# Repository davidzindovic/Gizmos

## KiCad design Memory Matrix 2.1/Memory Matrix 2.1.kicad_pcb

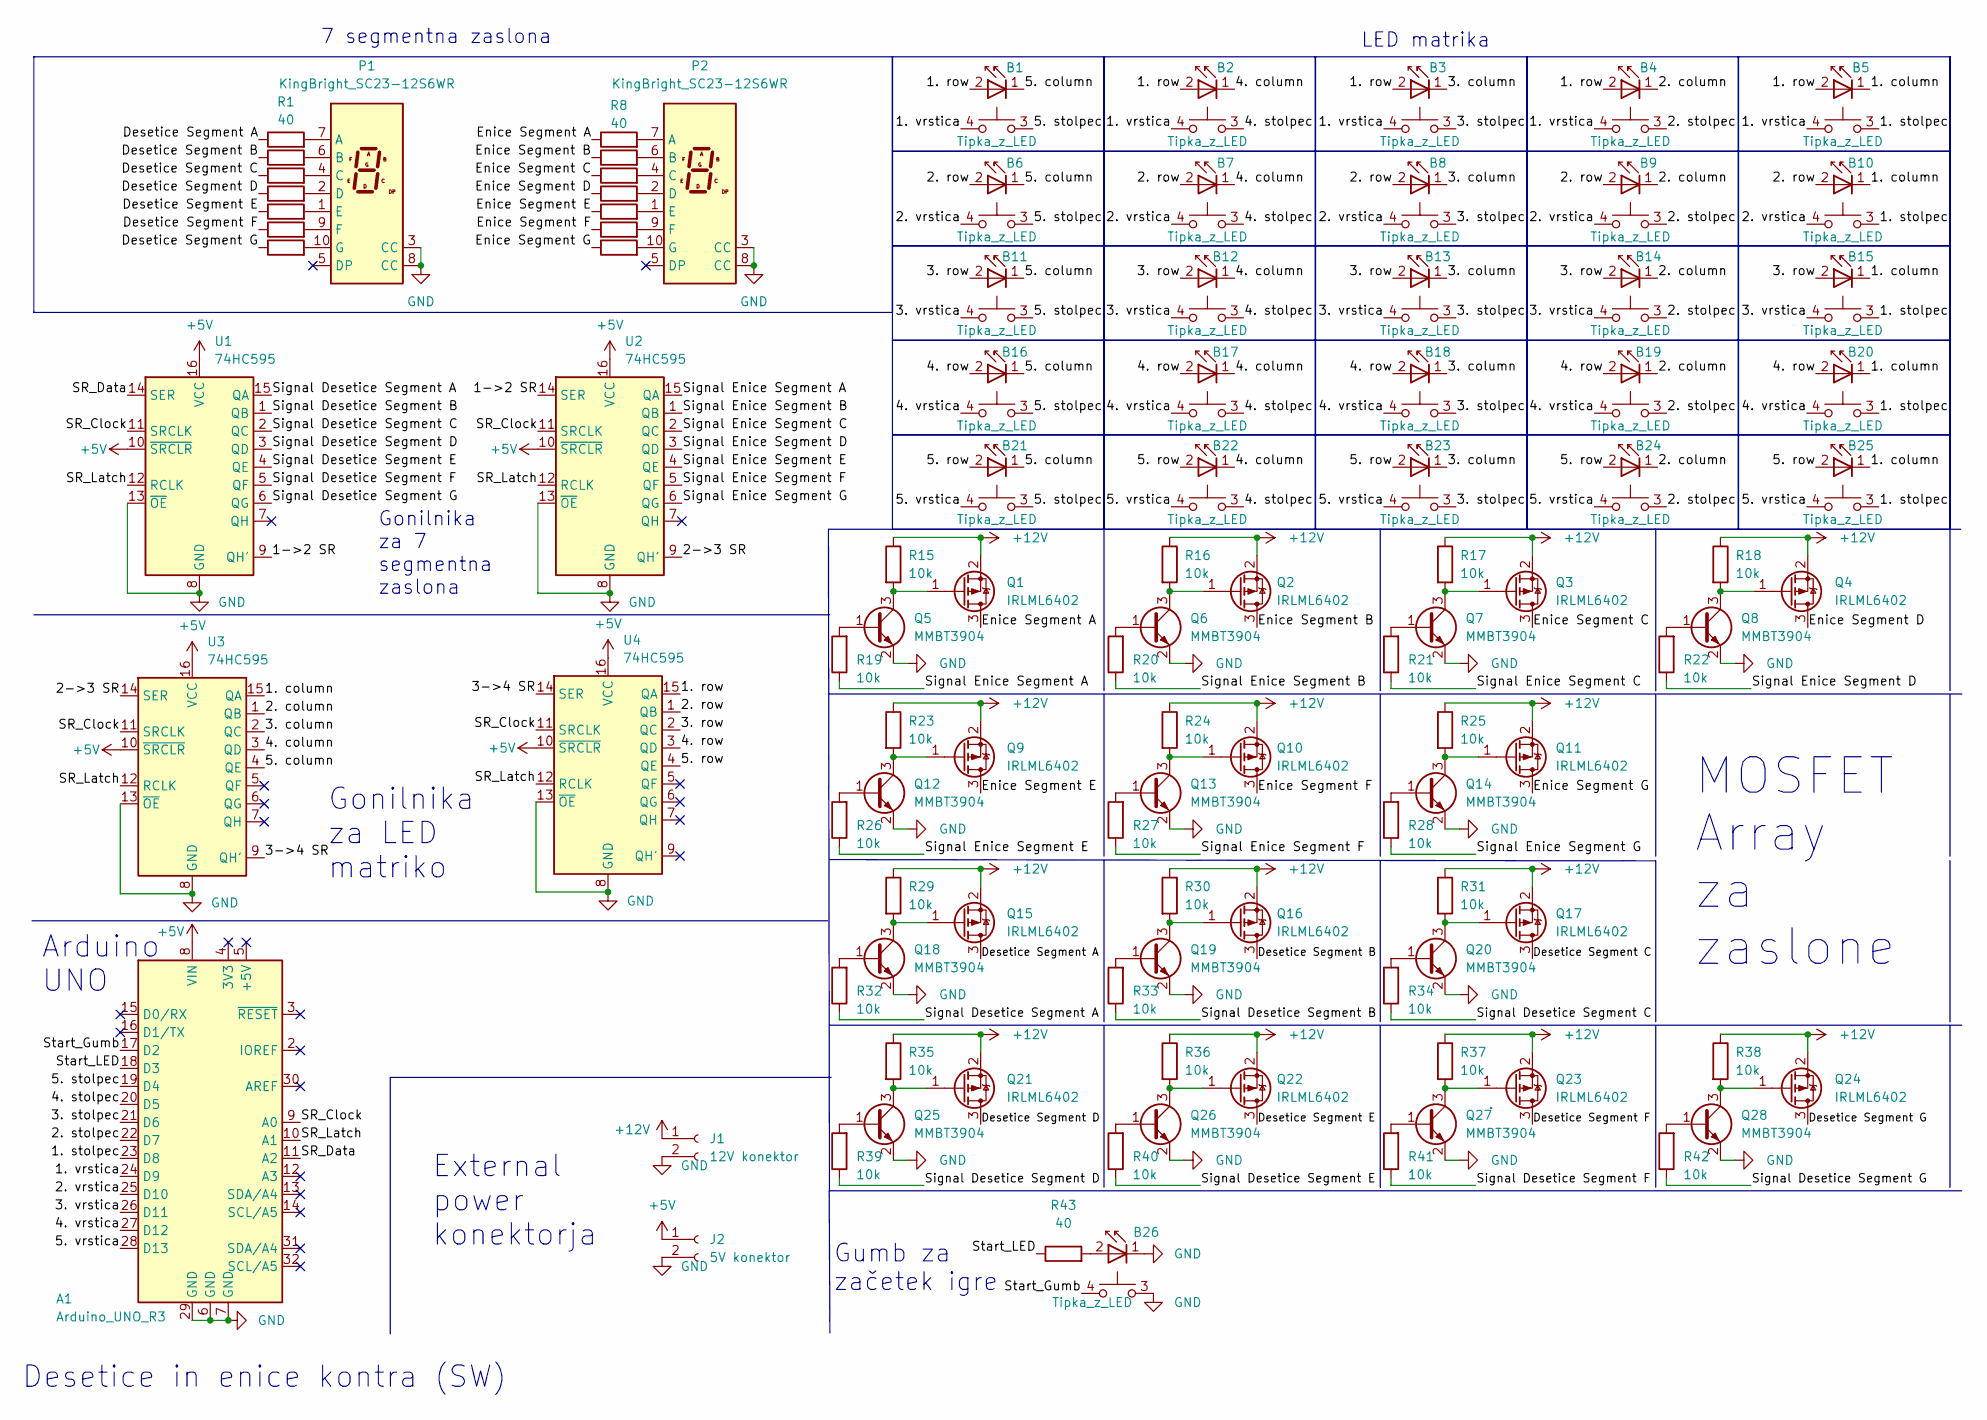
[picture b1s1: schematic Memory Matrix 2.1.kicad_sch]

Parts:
A1: Arduino_UNO_R3; Arduino_UNO_R3_WithMountingHoles
B1, B2, B3, B4, B5, B6, B7, B8, B9, B10, B11, B12, B13, B14, B15, B16, B17, B18, B19, B20, B21, B22, B23, B24, B25: Tipka_z_LED; Phoenix 4 pin z natičom
B26: Tipka_z_LED; PhoenixContact_MC_1,5_4-GF-3.81_1x04_P3.81mm_Horizontal_Thr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
J1: 12V konektor; PhoenixContact_MCV_1,5_2-GF-3.81_1x02_P3.81mm_Vertical_Thre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
J2: 5V konektor; PhoenixContact_MCV_1,5_2-GF-3.81_1x02_P3.81mm_Vertical_Thre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
P1, P2: KingBright_SC23-12S6WR; KingBright SC23-12S6WR
Q1, Q2, Q3, Q4, Q9, Q10, Q11, Q15, Q16, Q17, Q21, Q22, Q23, Q24: IRLML6402; SOT-23
Q5, Q6, Q7, Q8, Q12, Q13, Q14, Q18, Q19, Q20, Q25, Q26, Q27, Q28: MMBT3904; SOT-23
R1, R2, R3, R4, R5, R6, R7, R8, R9, R10, R11, R12, R13, R14, R43: 40; R_0805_2012Metric
R15, R16, R17, R18, R19, R20, R21, R22, R23, R24, R25, R26, R27, R28, R29, R30, R31, R32, R33, R34, R35, R36, R37, R38, R39, R40, R41, R42: 10k; R_0805_2012Metric
U1, U2, U3, U4: 74HC595; SOIC-16_3.9x9.9mm_P1.27mm

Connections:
+5V: A1.8 (VIN), J2.1, U1.10 (~SRCLR), U1.16 (VCC), U2.10 (~SRCLR), U2.16 (VCC), U3.10 (~SRCLR), U3.16 (VCC), U4.10 (~SRCLR), U4.16 (VCC)
+12V: J1.1, Q1.2 (S), Q2.2 (S), Q3.2 (S), Q4.2 (S), Q9.2 (S), Q10.2 (S), Q11.2 (S), Q15.2 (S), Q16.2 (S), Q17.2 (S), Q21.2 (S), Q22.2 (S), Q23.2 (S), Q24.2 (S), R15.1, R16.1, R17.1, R18.1, R23.1, R24.1, R25.1, R29.1, R30.1, R31.1, R35.1, R36.1, R37.1, R38.1
/1->2 SR: U1.9 (QH'), U2.14 (SER)
/1. column: B5.1, B10.1, B15.1, B20.1, B25.1, U3.15 (QA)
/1. row: B1.2, B2.2, B3.2, B4.2, B5.2, U4.15 (QA)
/1. stolpec: A1.23 (D8), B5.3, B10.3, B15.3, B20.3, B25.3
/1. vrstica: A1.24 (D9), B1.4, B2.4, B3.4, B4.4, B5.4
/2->3 SR: U2.9 (QH'), U3.14 (SER)
/2. column: B4.1, B9.1, B14.1, B19.1, B24.1, U3.1 (QB)
/2. row: B6.2, B7.2, B8.2, B9.2, B10.2, U4.1 (QB)
/2. stolpec: A1.22 (D7), B4.3, B9.3, B14.3, B19.3, B24.3
/2. vrstica: A1.25 (D10), B6.4, B7.4, B8.4, B9.4, B10.4
/3->4 SR: U3.9 (QH'), U4.14 (SER)
/3. column: B3.1, B8.1, B13.1, B18.1, B23.1, U3.2 (QC)
/3. row: B11.2, B12.2, B13.2, B14.2, B15.2, U4.2 (QC)
/3. stolpec: A1.21 (D6), B3.3, B8.3, B13.3, B18.3, B23.3
/3. vrstica: A1.26 (D11), B11.4, B12.4, B13.4, B14.4, B15.4
/4. column: B2.1, B7.1, B12.1, B17.1, B22.1, U3.3 (QD)
/4. row: B16.2, B17.2, B18.2, B19.2, B20.2, U4.3 (QD)
/4. stolpec: A1.20 (D5), B2.3, B7.3, B12.3, B17.3, B22.3
/4. vrstica: A1.27 (D12), B16.4, B17.4, B18.4, B19.4, B20.4
/5. column: B1.1, B6.1, B11.1, B16.1, B21.1, U3.4 (QE)
/5. row: B21.2, B22.2, B23.2, B24.2, B25.2, U4.4 (QE)
/5. stolpec: A1.19 (D4), B1.3, B6.3, B11.3, B16.3, B21.3
/5. vrstica: A1.28 (D13), B21.4, B22.4, B23.4, B24.4, B25.4
/Desetice Segment A: Q15.3 (D), R1.1
/Desetice Segment B: Q16.3 (D), R2.1
/Desetice Segment C: Q17.3 (D), R3.1
/Desetice Segment D: Q21.3 (D), R4.1
/Desetice Segment E: Q22.3 (D), R5.1
/Desetice Segment F: Q23.3 (D), R6.1
/Desetice Segment G: Q24.3 (D), R7.1
/Enice Segment A: Q1.3 (D), R8.1
/Enice Segment B: Q2.3 (D), R9.1
/Enice Segment C: Q3.3 (D), R10.1
/Enice Segment D: Q4.3 (D), R11.1
/Enice Segment E: Q9.3 (D), R12.1
/Enice Segment F: Q10.3 (D), R13.1
/Enice Segment G: Q11.3 (D), R14.1
/SR_Clock: A1.9 (A0), U1.11 (SRCLK), U2.11 (SRCLK), U3.11 (SRCLK), U4.11 (SRCLK)
/SR_Data: A1.11 (A2), U1.14 (SER)
/SR_Latch: A1.10 (A1), U1.12 (RCLK), U2.12 (RCLK), U3.12 (RCLK), U4.12 (RCLK)
/Signal Desetice Segment A: R32.1, U1.15 (QA)
/Signal Desetice Segment B: R33.1, U1.1 (QB)
/Signal Desetice Segment C: R34.1, U1.2 (QC)
/Signal Desetice Segment D: R39.1, U1.3 (QD)
/Signal Desetice Segment E: R40.1, U1.4 (QE)
/Signal Desetice Segment F: R41.1, U1.5 (QF)
/Signal Desetice Segment G: R42.1, U1.6 (QG)
/Signal Enice Segment A: R19.1, U2.15 (QA)
/Signal Enice Segment B: R20.1, U2.1 (QB)
/Signal Enice Segment C: R21.1, U2.2 (QC)
/Signal Enice Segment D: R22.1, U2.3 (QD)
/Signal Enice Segment E: R26.1, U2.4 (QE)
/Signal Enice Segment F: R27.1, U2.5 (QF)
/Signal Enice Segment G: R28.1, U2.6 (QG)
/Start_Gumb: A1.17 (D2), B26.4
/Start_LED: A1.18 (D3), R43.1
GND: A1.6 (GND), A1.7 (GND), A1.29 (GND), B26.1, B26.3, J1.2, J2.2, P1.3 (CC), P1.8 (CC), P2.3 (CC), P2.8 (CC), Q5.2 (E), Q6.2 (E), Q7.2 (E), Q8.2 (E), Q12.2 (E), Q13.2 (E), Q14.2 (E), Q18.2 (E), Q19.2 (E), Q20.2 (E), Q25.2 (E), Q26.2 (E), Q27.2 (E), Q28.2 (E), U1.8 (GND), U1.13 (~OE), U2.8 (GND), U2.13 (~OE), U3.8 (GND), U3.13 (~OE), U4.8 (GND), U4.13 (~OE)
unnamed: B26.2, R43.2
unnamed: P1.1 (E), R5.2
unnamed: P1.2 (D), R4.2
unnamed: P1.4 (C), R3.2
unnamed: P1.6 (B), R2.2
unnamed: P1.7 (A), R1.2
unnamed: P1.9 (F), R6.2
unnamed: P1.10 (G), R7.2
unnamed: P2.1 (E), R12.2
unnamed: P2.2 (D), R11.2
unnamed: P2.4 (C), R10.2
unnamed: P2.6 (B), R9.2
unnamed: P2.7 (A), R8.2
unnamed: P2.9 (F), R13.2
unnamed: P2.10 (G), R14.2
unnamed: Q1.1 (G), Q5.3 (C), R15.2
unnamed: Q2.1 (G), Q6.3 (C), R16.2
unnamed: Q3.1 (G), Q7.3 (C), R17.2
unnamed: Q4.1 (G), Q8.3 (C), R18.2
unnamed: Q5.1 (B), R19.2
unnamed: Q6.1 (B), R20.2
unnamed: Q7.1 (B), R21.2
unnamed: Q8.1 (B), R22.2
unnamed: Q10.1 (G), Q13.3 (C), R24.2
unnamed: Q11.1 (G), Q14.3 (C), R25.2
unnamed: Q12.1 (B), R26.2
unnamed: Q9.1 (G), Q12.3 (C), R23.2
unnamed: Q13.1 (B), R27.2
unnamed: Q14.1 (B), R28.2
unnamed: Q15.1 (G), Q18.3 (C), R29.2
unnamed: Q16.1 (G), Q19.3 (C), R30.2
unnamed: Q17.1 (G), Q20.3 (C), R31.2
unnamed: Q18.1 (B), R32.2
unnamed: Q19.1 (B), R33.2
unnamed: Q20.1 (B), R34.2
unnamed: Q21.1 (G), Q25.3 (C), R35.2
unnamed: Q22.1 (G), Q26.3 (C), R36.2
unnamed: Q23.1 (G), Q27.3 (C), R37.2
unnamed: Q24.1 (G), Q28.3 (C), R38.2
unnamed: Q25.1 (B), R39.2
unnamed: Q26.1 (B), R40.2
unnamed: Q27.1 (B), R41.2
unnamed: Q28.1 (B), R42.2

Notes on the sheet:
Gonilnika za LED matriko
LED matrika
7 segmentna zaslona
External power konektorja
MOSFET Array za zaslone
Gumb za začetek igre
Arduino UNO
Desetice in enice kontra (SW)
Gonilnika za 7 segmentna zaslona

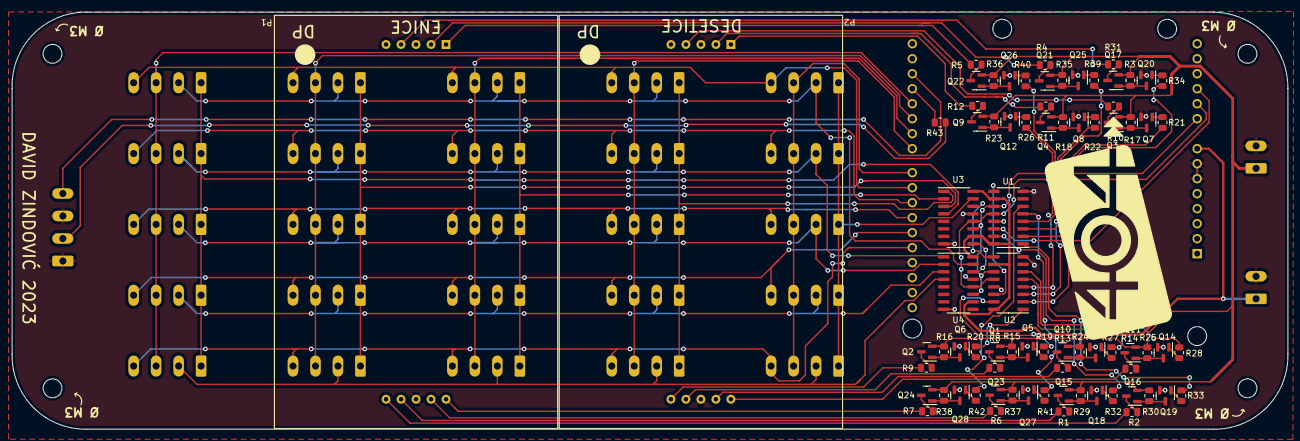
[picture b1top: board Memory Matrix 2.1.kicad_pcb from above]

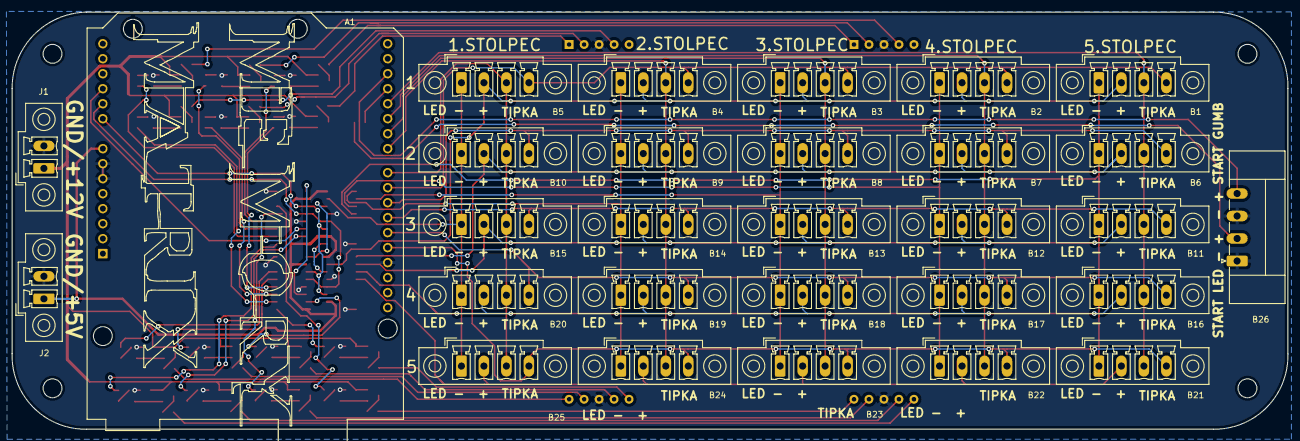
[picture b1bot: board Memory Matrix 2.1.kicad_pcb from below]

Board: 2 copper layers, 216.1 x 70.7 mm, 106 parts (29 on the bottom side), 102 nets.

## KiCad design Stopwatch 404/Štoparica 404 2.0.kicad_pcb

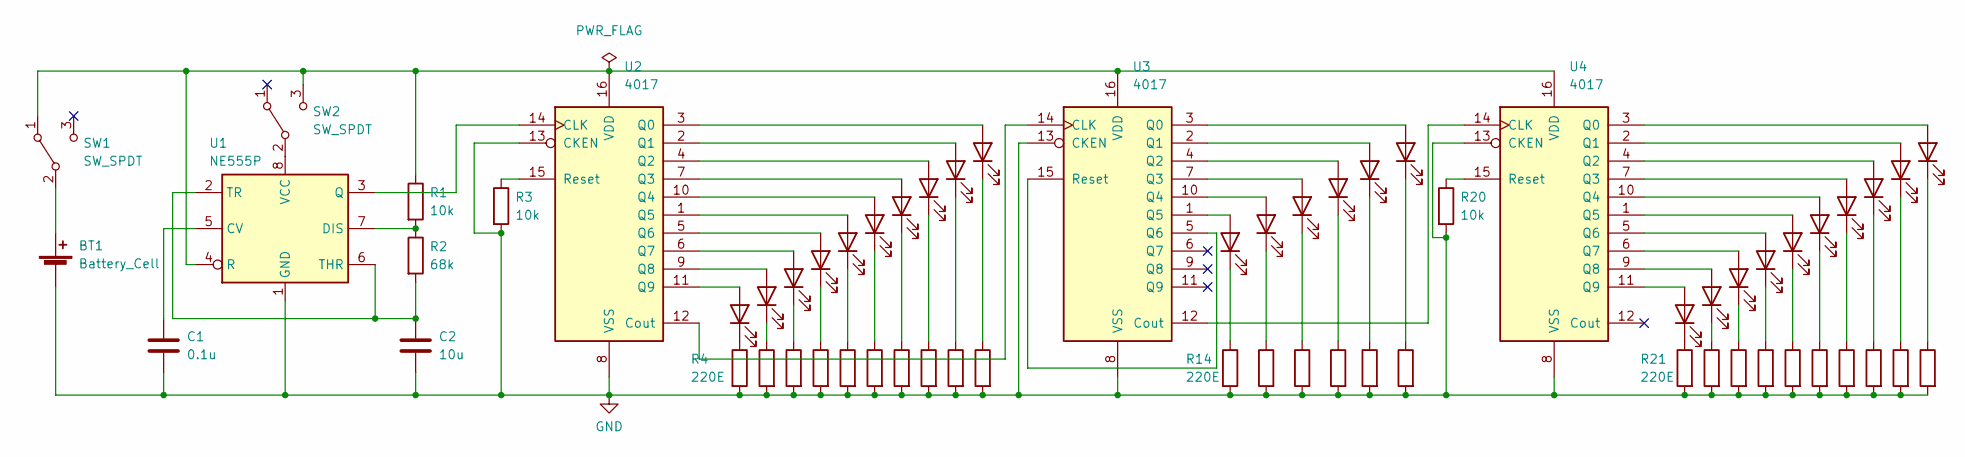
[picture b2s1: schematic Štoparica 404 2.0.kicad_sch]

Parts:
BT1: Battery_Cell; BatteryHolder_Eagle_12BH611-GR
C1: 0.1u; C_Disc_D4.7mm_W2.5mm_P5.00mm
C2: 10u; C_Disc_D4.7mm_W2.5mm_P5.00mm
D1, D2, D3, D4, D5, D6, D7, D8, D9, D10, D11, D12, D13, D14, D15, D16, D17, D18, D19, D20, D21, D22, D23, D24, D25, D26: LED; LED_D5.0mm
R1, R3, R20: 10k; R_Axial_DIN0204_L3.6mm_D1.6mm_P7.62mm_Horizontal
R2: 68k; R_Axial_DIN0204_L3.6mm_D1.6mm_P7.62mm_Horizontal
R4, R5, R6, R7, R8, R9, R10, R11, R12, R13, R14, R15, R16, R17, R18, R19, R21, R22, R23, R24, R25, R26, R27, R28, R29, R30: 220E; R_Axial_DIN0204_L3.6mm_D1.6mm_P7.62mm_Horizontal
SW1, SW2: SW_SPDT; PinHeader_1x03_P2.54mm_Horizontal
U1: NE555P; DIP-8_W7.62mm
U2, U3, U4: 4017; DIP-16_W7.62mm

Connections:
GND: BT1.2 (-), C1.2, C2.2, R3.2, R4.2, R5.2, R6.2, R7.2, R8.2, R9.2, R10.2, R11.2, R12.2, R13.2, R14.2, R15.2, R16.2, R17.2, R18.2, R19.2, R20.2, R21.2, R22.2, R23.2, R24.2, R25.2, R26.2, R27.2, R28.2, R29.2, R30.2, U1.1 (GND), U2.8 (VSS), U2.13 (CKEN), U3.8 (VSS), U3.13 (CKEN), U4.8 (VSS), U4.13 (CKEN)
unnamed: BT1.1 (+), SW1.2 (B)
unnamed: D1.2 (A), U2.11 (Q9)
unnamed: D1.1 (K), R4.1
unnamed: D2.2 (A), U2.9 (Q8)
unnamed: D2.1 (K), R5.1
unnamed: D3.2 (A), U2.6 (Q7)
unnamed: D3.1 (K), R6.1
unnamed: D4.2 (A), U2.5 (Q6)
unnamed: D4.1 (K), R7.1
unnamed: D5.2 (A), U2.1 (Q5)
unnamed: D5.1 (K), R8.1
unnamed: D6.2 (A), U2.10 (Q4)
unnamed: D6.1 (K), R9.1
unnamed: D7.2 (A), U2.7 (Q3)
unnamed: D7.1 (K), R10.1
unnamed: D8.2 (A), U2.4 (Q2)
unnamed: D8.1 (K), R11.1
unnamed: D9.2 (A), U2.2 (Q1)
unnamed: D9.1 (K), R12.1
unnamed: D10.2 (A), U2.3 (Q0)
unnamed: D10.1 (K), R13.1
unnamed: D11.2 (A), U3.1 (Q5)
unnamed: D11.1 (K), R14.1
unnamed: D12.2 (A), U3.10 (Q4)
unnamed: D12.1 (K), R15.1
unnamed: D13.2 (A), U3.7 (Q3)
unnamed: D13.1 (K), R16.1
unnamed: D14.2 (A), U3.4 (Q2)
unnamed: D14.1 (K), R17.1
unnamed: D15.2 (A), U3.2 (Q1)
unnamed: D15.1 (K), R18.1
unnamed: D16.2 (A), U3.3 (Q0)
unnamed: D16.1 (K), R19.1
unnamed: D17.2 (A), U4.11 (Q9)
unnamed: D17.1 (K), R21.1
unnamed: D18.2 (A), U4.9 (Q8)
unnamed: D18.1 (K), R22.1
unnamed: D19.2 (A), U4.6 (Q7)
unnamed: D19.1 (K), R23.1
unnamed: D20.2 (A), U4.5 (Q6)
unnamed: D20.1 (K), R24.1
unnamed: D21.2 (A), U4.1 (Q5)
unnamed: D21.1 (K), R25.1
unnamed: D22.2 (A), U4.10 (Q4)
unnamed: D22.1 (K), R26.1
unnamed: D23.2 (A), U4.7 (Q3)
unnamed: D23.1 (K), R27.1
unnamed: D24.2 (A), U4.4 (Q2)
unnamed: D24.1 (K), R28.1
unnamed: D25.2 (A), U4.2 (Q1)
unnamed: D25.1 (K), R29.1
unnamed: D26.2 (A), U4.3 (Q0)
unnamed: D26.1 (K), R30.1
unnamed: R1.1, SW1.1 (A), SW2.3 (C), U1.4 (R), U2.16 (VDD), U3.16 (VDD), U4.16 (VDD)
unnamed: SW2.2 (B), U1.8 (VCC)
unnamed: C1.1, U1.5 (CV)
unnamed: R1.2, R2.1, U1.7 (DIS)
unnamed: U1.3 (Q), U2.14 (CLK)
unnamed: C2.1, R2.2, U1.2 (TR), U1.6 (THR)
unnamed: U2.12 (Cout), U3.14 (CLK)
unnamed: R3.1, U2.15 (Reset)
unnamed: U3.12 (Cout), U4.14 (CLK)
unnamed: U3.5 (Q6), U3.15 (Reset)
unnamed: R20.1, U4.15 (Reset)

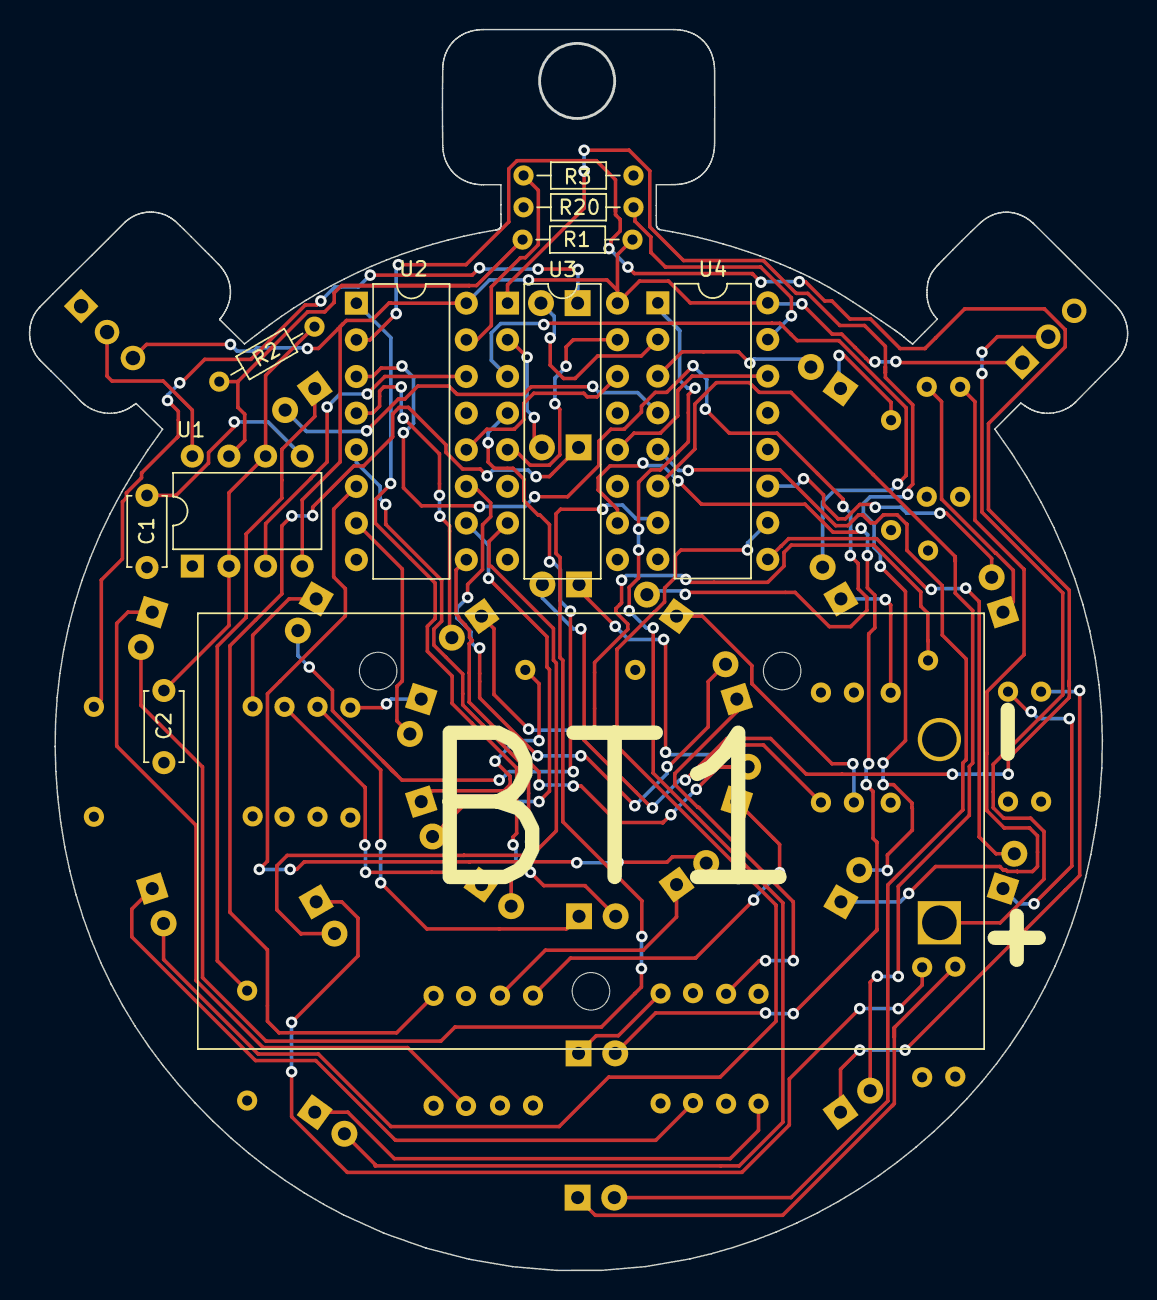
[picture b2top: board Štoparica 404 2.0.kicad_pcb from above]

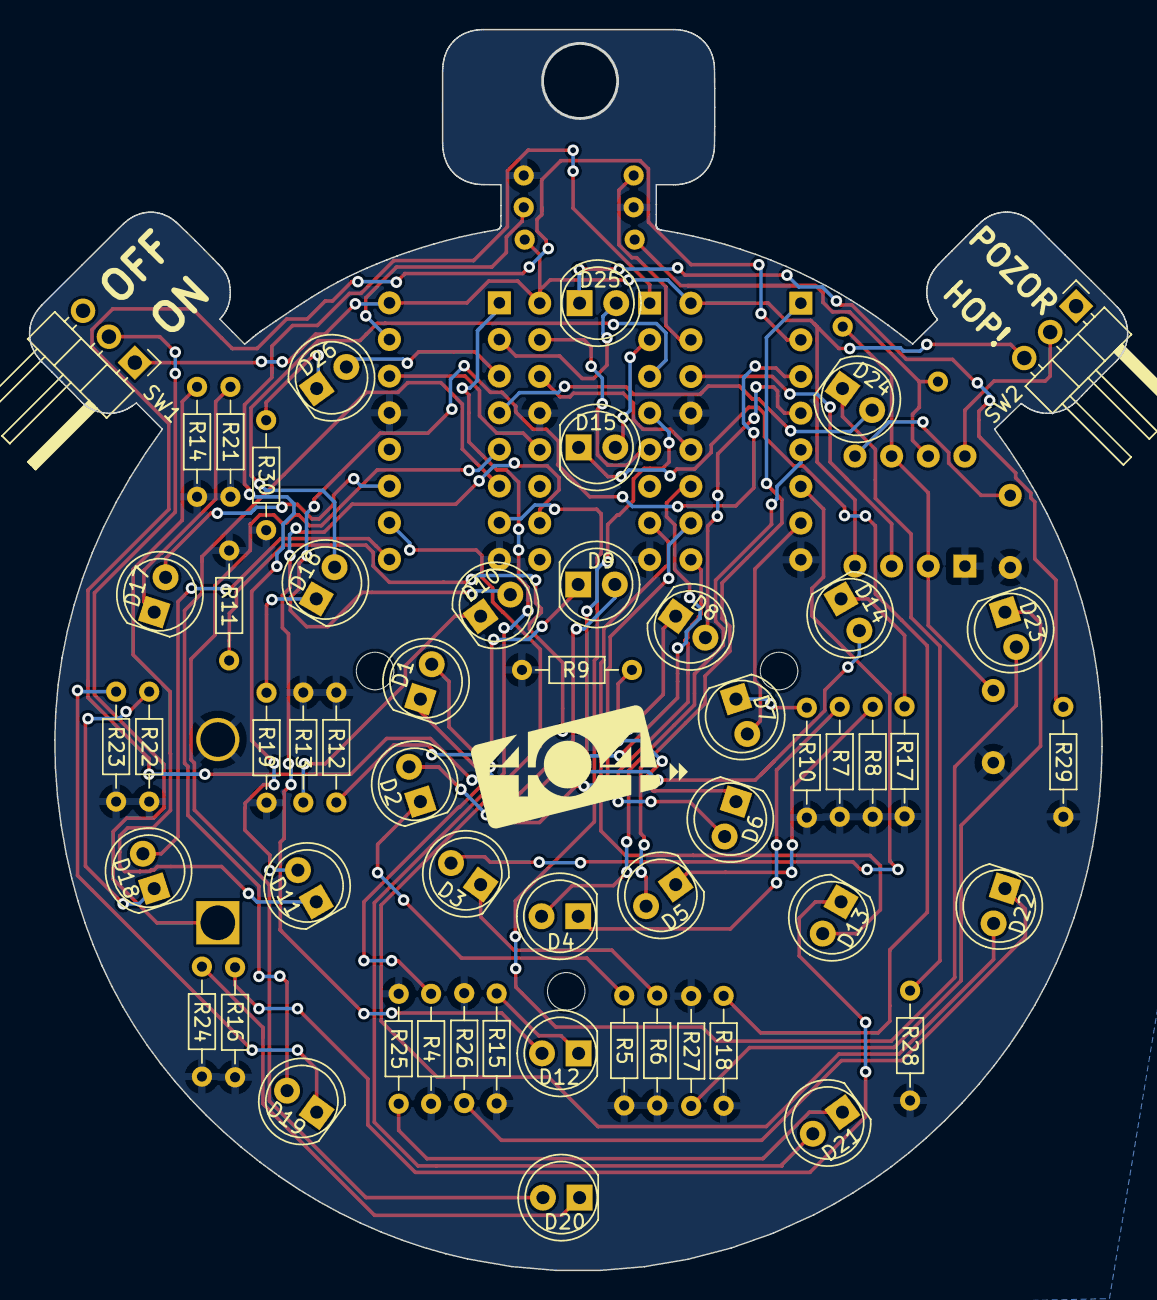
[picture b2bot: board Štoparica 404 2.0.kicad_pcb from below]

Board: 2 copper layers, 76.1 x 86.0 mm, 65 parts (54 on the bottom side), 65 nets.

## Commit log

2026-05-28 Rename LIDL_U_lock_holder/Assembly1.iam to Bike_parts/LIDL_U_lock_holder/Assembly1.iam
